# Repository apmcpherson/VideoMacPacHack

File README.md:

# VideoMacPacHack

The VideoMacPacHack is a clone of the Video Mac Pac, a PDS video card for the Macintosh Portable designed in 1991 by Computer Care Inc. The Video Mac Pac provides monochrome (1-bit) video on an external display, with several resolutions selectable by a control panel.

The VideoMacPacHack aims to replicate the Video Mac Pac using original parts where possible, with modern substitutions in  cases where original parts are hard to source (e.g. GAL, miniature relay), or where the original design was unknown (the video adapter board).

## Contents

* `hardware/VideoMacPac`: PCB design for the VideoMacPacHack, 4 layers, made in Kicad
* `hardware/VGA_adapter`: PCB design for the VGA breakout board, 2 layers, made in EAGLE
* `software`: Video Mac Pac Control Panel, needed to load the card firmware and select resolution
* `photos`: Photos of the original and clone card
* `documentation`: Technical information on the hardware and software

## System Requirements and Operation

The VideoMacPacHack fits the PDS slot of the Macintosh Portable. It has been successfully tested in both M5120 (non-backlit) and M5126 (backlit) Portables. Based on the address space used by the card, it will probably only work on Portables with less than 8MB of RAM installed.

The VideoMacPacHack (like the original Video Mac Pac) requires its associated control panel to run (see `software`). The external screen will become active when the control panel loads, provided the external video adapter is attached at boot. If the Portable is put to sleep, the external display will not work until reboot.

## Acknowledgments

The Video Mac Pac was created by Computer Care Inc. in 1991, apparently based on the Lapis DisplayServer.

The VideoMacPacHack was designed by [Andrew McPherson](https://github.com/apmcpherson) with encouragement from [Tom Stepleton](https://github.com/stepleton) based on hardware in his collection. In the interest of historical preservation it is released into the public domain, with no warranty of any sort.

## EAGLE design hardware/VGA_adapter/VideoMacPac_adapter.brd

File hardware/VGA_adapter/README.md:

# VideoMacPac video adapter

These design materials are in the public domain, with no warranty whatsoever. See `documentation` on this repository for further design notes and `photos` for a photo of the assembled board.

## EAGLE files

* `VideoMacPac_adapter.sch`: EAGLE schematic
* `VideoMacPac_adapter.brd`: EAGLE PCB design
* `schematic.png`: image of the schematic

## Gerbers

This is a 2-layer PCB which can be fabricated from the files in the `gerbers` directory. It is a simple design which can be made on a mill with no soldermask as long as it has plated-through holes. The most important files are:

* `copper_top.gbr`: top copper
* `copper_bottom.gbr`: bottom copper
* `profile.gbr`: board outline
* `drill_1_16.xln`: Excellon drill file

## Bill of Materials

| Name    | Value                                 |
| ------- | ------------------------------------- |
| C1-C2   | 0.1uF 0603 capacitors                 |
| IC1     | 74LVC245 (20-SOIC) bus transceiver    |
| IC2     | MCP1700-3302T (SOT23) 3.3V regulator  |
| J1      | DB25 female                           |
| J2      | HD15 (VGA) female                     |
| R1-R3   | 133 ohm 0603 resistors                |
| R4-R6   | 150 ohm 0603 resistors                |
| R7      | 100 ohm 0603 resistor (could use 150) |

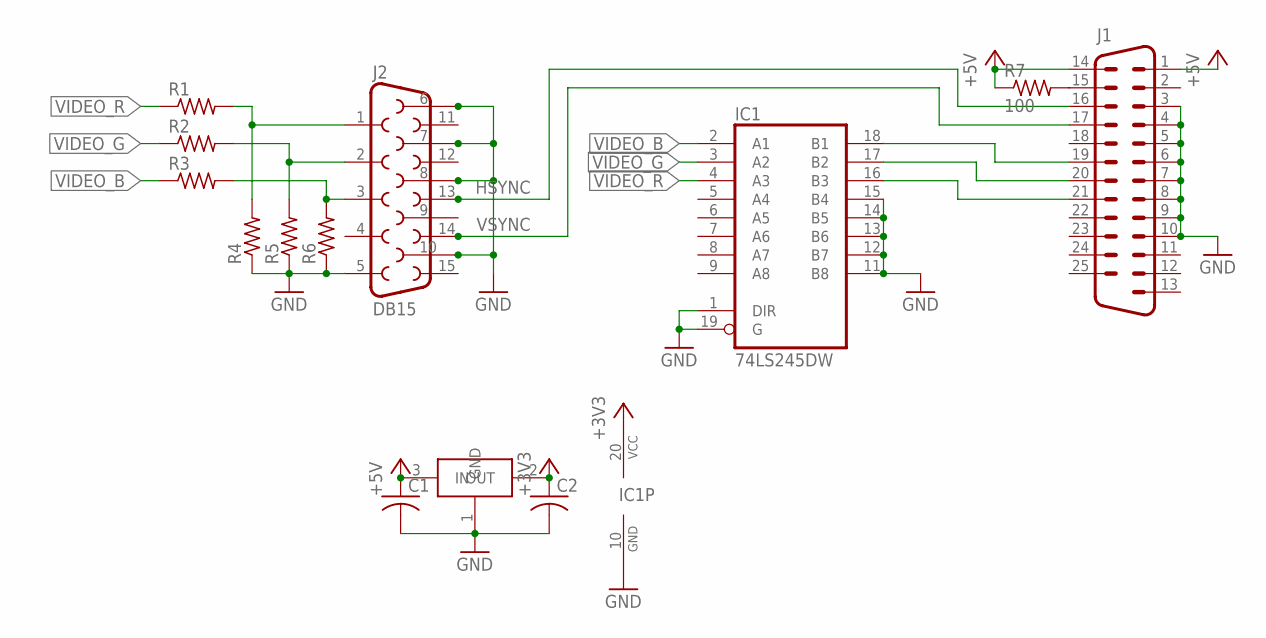
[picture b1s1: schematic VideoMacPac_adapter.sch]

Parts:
C1, C2: C-USC0603; C0603
IC1: 74LS245DW; SO20W
IC2: MCP1700; SOT23
J1: DB25H; M25H
J2: DB15
R1, R2, R3, R4, R5, R6: R-US_R0603; R0603
R7: 100; R0603

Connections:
+3V3: C2.1, IC1.20 (VCC), IC2.2 (OUT)
+5V: C1.1, IC2.3 (IN), J1.1, J1.14, R7.1
GND: C1.2, C2.2, IC1.1 (DIR), IC1.10 (GND), IC1.11 (B8), IC1.12 (B7), IC1.13 (B6), IC1.14 (B5), IC1.15 (B4), IC1.19 (G), IC2.1 (GND), J1.3, J1.4, J1.5, J1.6, J1.7, J1.8, J1.9, J1.10, J2.5, J2.6, J2.7, J2.8, J2.10, R4.1, R5.1, R6.1
HSYNC: J1.16, J2.13
unnamed: J1.15, R7.2
unnamed: IC1.16 (B3), J1.21
unnamed: J2.3, R3.2, R6.2
unnamed: IC1.17 (B2), J1.20
unnamed: J2.2, R2.2, R5.2
unnamed: J2.1, R1.2, R4.2
unnamed: IC1.18 (B1), J1.19
VIDEO_B: IC1.2 (A1), R3.1
VIDEO_G: IC1.3 (A2), R2.1
VIDEO_R: IC1.4 (A3), R1.1
VSYNC: J1.17, J2.14

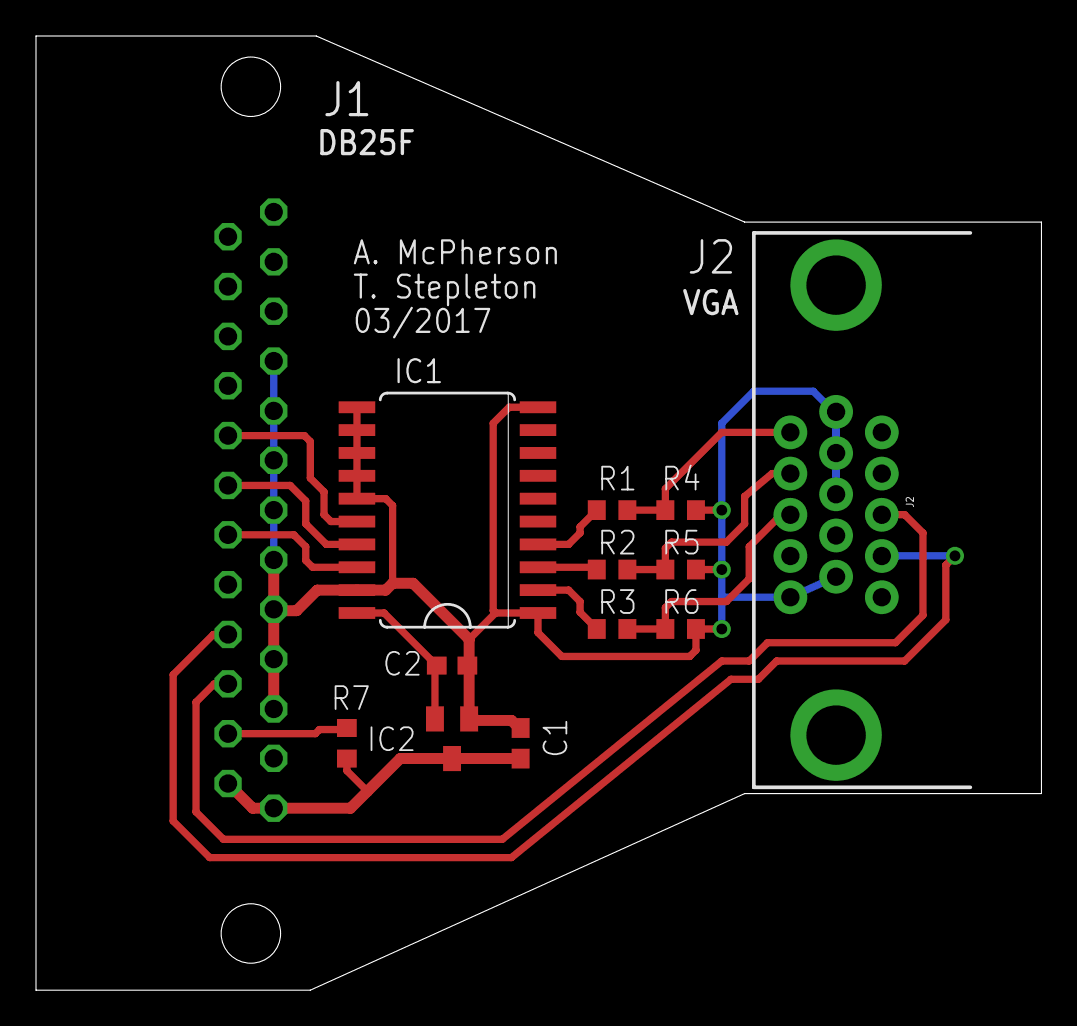
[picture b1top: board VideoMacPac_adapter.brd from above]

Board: 2 copper layers, 55.9 x 53.0 mm, 13 parts (1 on the bottom side), 15 nets.

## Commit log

2020-04-06 Added documentation on VMP hardware and software
2020-04-06 Added documentation on the VMPH and adapter
2020-04-06 Added README to VMPH design
2020-04-06 Added README for VGA adapter
2020-04-06 Added README to documentation
2020-04-06 Added photo to main README
2020-04-06 URL fix for README photo

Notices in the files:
parts and their libraries:
SparkFun-Connectors: Licensing: Creative Commons ShareAlike 4.0 International - https://creativecommons.org/licenses/by-sa/4.0
